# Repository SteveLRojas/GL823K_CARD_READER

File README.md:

# GL823K_CARD_READER
Full-size SD card reader using GL823K

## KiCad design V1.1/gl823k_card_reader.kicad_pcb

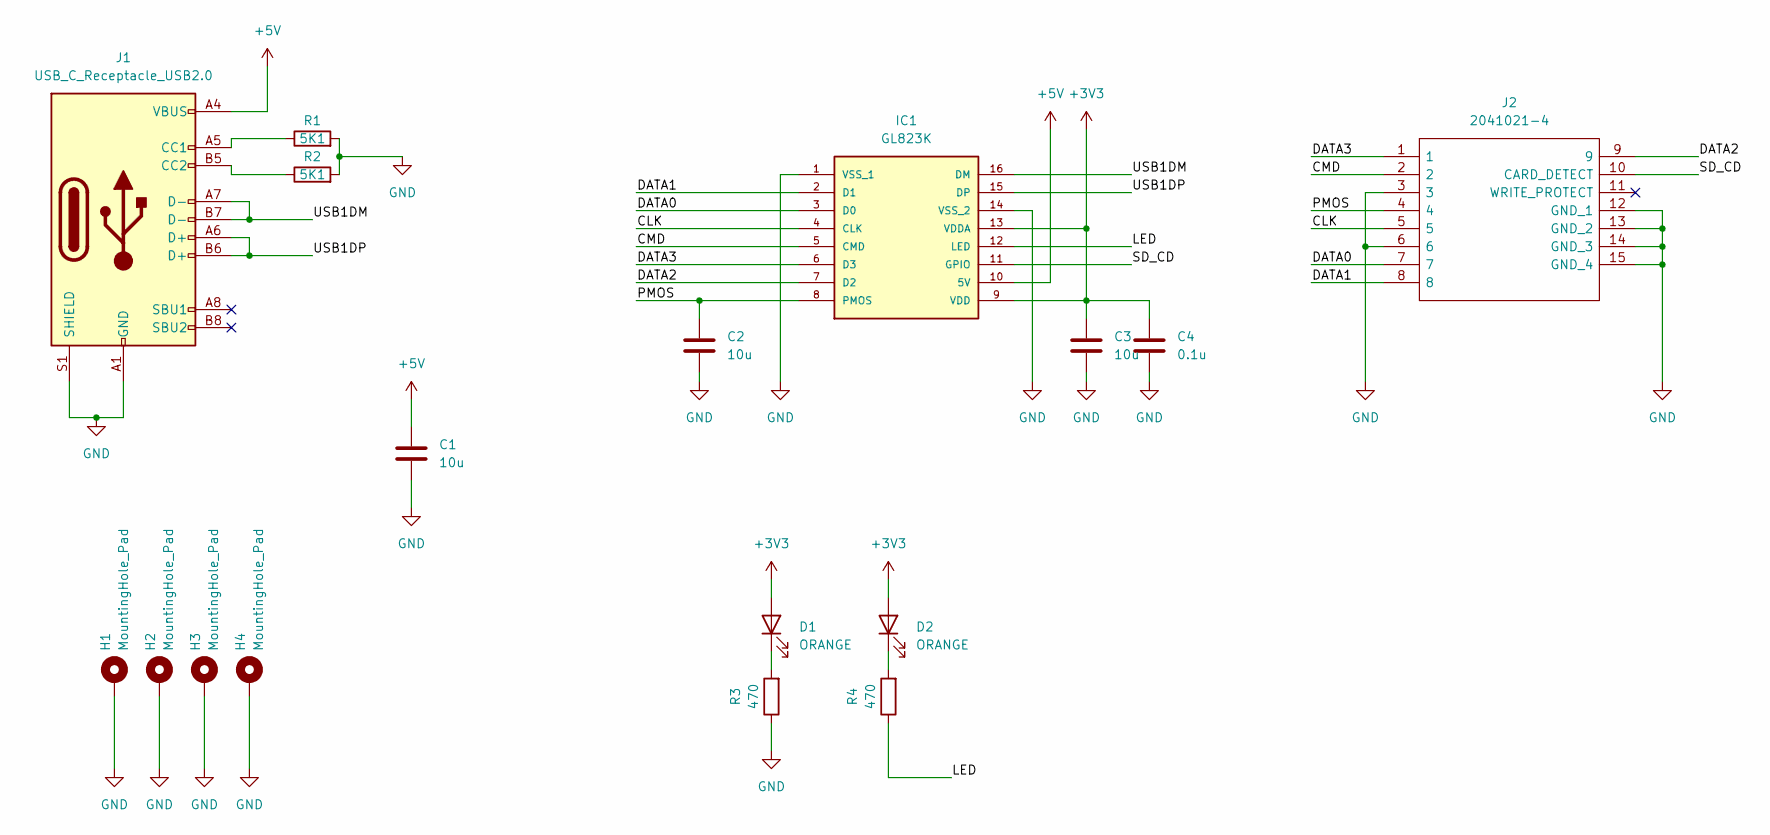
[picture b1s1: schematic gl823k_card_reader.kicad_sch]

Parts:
C1, C2, C3: 10u; C_1206_3216Metric
C4: 0.1u; C_0805_2012Metric
D1, D2: ORANGE; LED_0805_2012Metric
H1, H2, H3, H4: MountingHole_Pad; MountingHole_3.2mm_M3_Pad
IC1: GL823K; SSOP-16_3.9x4.9mm_P0.635mm; MANUFACTURER_PART_NUMBER GL823K
J1: USB_C_Receptacle_USB2.0; USB_C_Receptacle_HRO_TYPE-C-31-M-12
J2: 2041021-4; 20410214; Mouser Part Number 571-2041021-4
R1, R2: 5K1; R_0805_2012Metric
R3, R4: 470; R_0805_2012Metric

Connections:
+3V3: C3.1, C4.1, D1.2 (A), D2.2 (A), IC1.9 (VDD), IC1.13 (VDDA)
+5V: C1.1, IC1.10 (5V), J1.A4 (VBUS), J1.A9 (VBUS), J1.B4 (VBUS), J1.B9 (VBUS)
/CLK: IC1.4 (CLK), J2.5
/CMD: IC1.5 (CMD), J2.2
/DATA0: IC1.3 (D0), J2.7
/DATA1: IC1.2 (D1), J2.8
/DATA2: IC1.7 (D2), J2.9
/DATA3: IC1.6 (D3), J2.1
/LED: IC1.12 (LED), R4.1
/PMOS: C2.1, IC1.8 (PMOS), J2.4
/SD_CD: IC1.11 (GPIO), J2.10 (CARD_DETECT)
/USB1DM: IC1.16 (DM), J1.A7 (D-), J1.B7 (D-)
/USB1DP: IC1.15 (DP), J1.A6 (D+), J1.B6 (D+)
GND: C1.2, C2.2, C3.2, C4.2, H1.1, H2.1, H3.1, H4.1, IC1.1 (VSS_1), IC1.14 (VSS_2), J1.A1 (GND), J1.A12 (GND), J1.B1 (GND), J1.B12 (GND), J1.S1 (SHIELD), J2.3, J2.6, J2.12 (GND_1), J2.13 (GND_2), J2.14 (GND_3), J2.15 (GND_4), R1.2, R2.2, R3.1
unnamed: D1.1 (K), R3.2
unnamed: D2.1 (K), R4.2
unnamed: J1.A5 (CC1), R1.1
unnamed: J1.B5 (CC2), R2.1

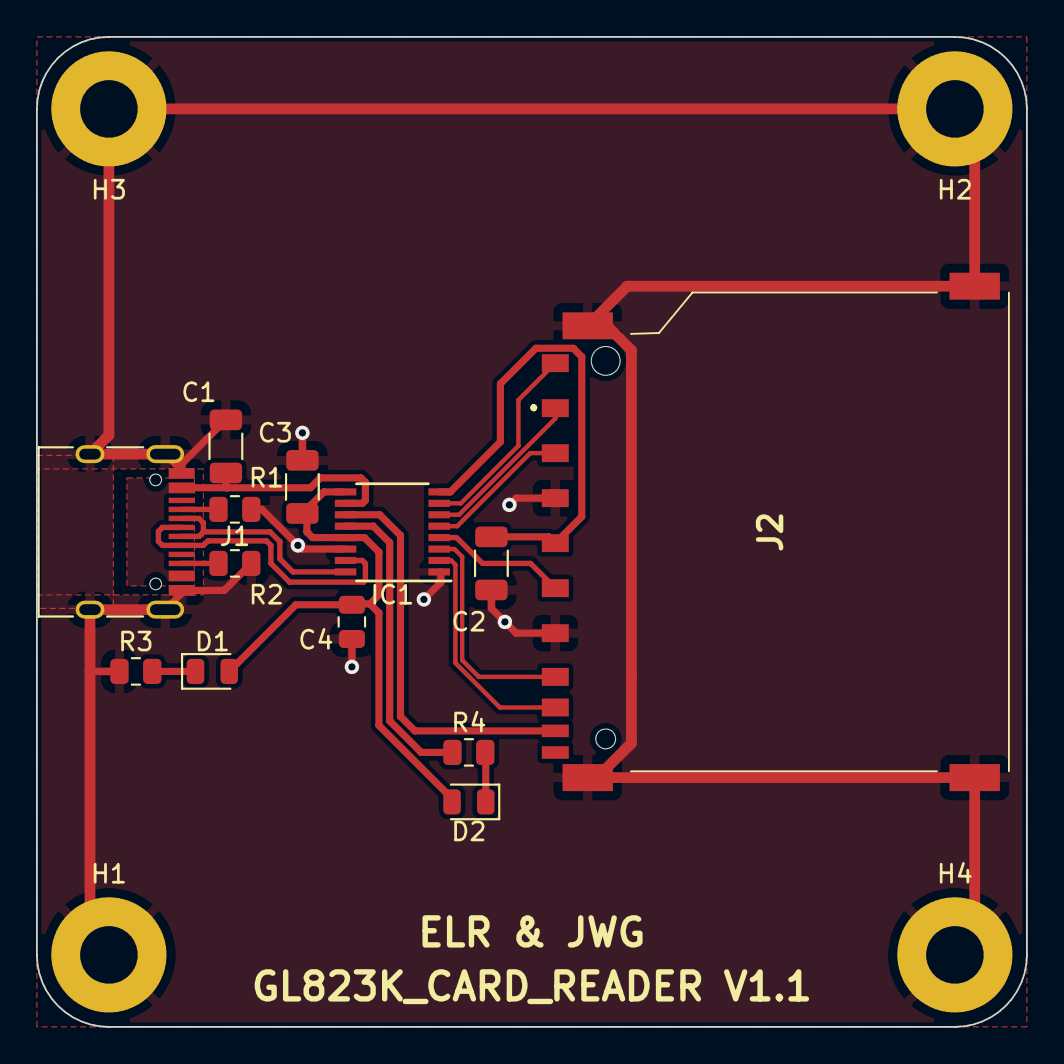
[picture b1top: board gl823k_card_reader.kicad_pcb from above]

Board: 2 copper layers, 55.0 x 55.0 mm, 17 parts (0 on the bottom side), 18 nets.

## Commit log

2024-08-03 Added license
